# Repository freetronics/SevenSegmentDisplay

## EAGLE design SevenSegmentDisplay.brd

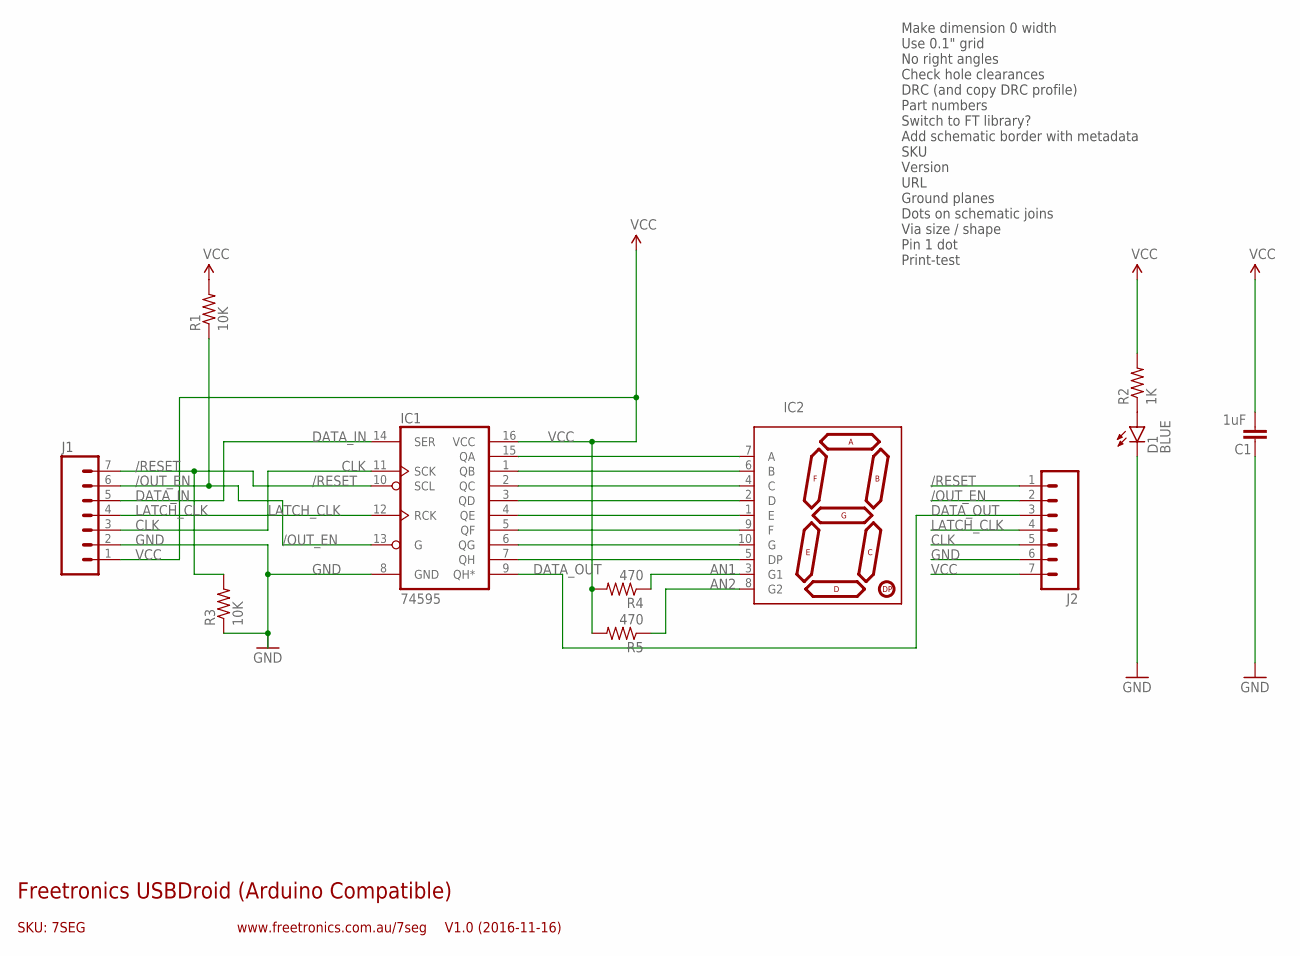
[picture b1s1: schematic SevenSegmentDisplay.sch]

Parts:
C1: 1uF; 0603-CAP
D1: BLUE; LED-0603
IC1: 74595; TSSOP16
IC2: 7-SEGMENT-DISPLAYPTH; 7-SEGMENT-DISPLAY
J1, J2: M07; 1X07
R1, R3: 10K; 0603-RES
R2: 1K; 0603-RES
R4, R5: 470; 0603-RES

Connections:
/OUT_EN: IC1.13 (G), J1.6, J2.2, R1.1
/RESET: IC1.10 (SCL), J1.7, J2.1, R3.2
AN1: IC2.3 (G1), R4.1
AN2: IC2.8 (G2), R5.1
CLK: IC1.11 (SCK), J1.3, J2.5
DATA_IN: IC1.14 (SER), J1.5
DATA_OUT: IC1.9 (QH*), J2.3
GND: C1.1, D1.C, IC1.8 (GND), J1.2, J2.6, R3.1
LATCH_CLK: IC1.12 (RCK), J1.4, J2.4
unnamed: IC1.15 (QA), IC2.7 (A)
unnamed: IC1.1 (QB), IC2.6 (B)
unnamed: IC1.2 (QC), IC2.4 (C)
unnamed: D1.A, R2.1
unnamed: IC1.3 (QD), IC2.2 (D)
unnamed: IC1.4 (QE), IC2.1 (E)
unnamed: IC1.5 (QF), IC2.9 (F)
unnamed: IC1.6 (QG), IC2.10 (G)
unnamed: IC1.7 (QH), IC2.5 (DP)
VCC: C1.2, IC1.16 (VCC), J1.1, J2.7, R1.2, R2.2, R4.2, R5.2

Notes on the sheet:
Make dimension 0 width Use 0.1" grid No right angles Check hole clearances DRC (and copy DRC profile) Part numbers Switch to FT library? Add schematic border with metadata SKU Version URL Ground planes Dots on schematic joins Via size / shape Pin 1 dot Print-test
Freetronics USBDroid (Arduino Compatible)
V1.0 (2016-11-16)
www.freetronics.com.au/7seg
SKU: 7SEG
IC2

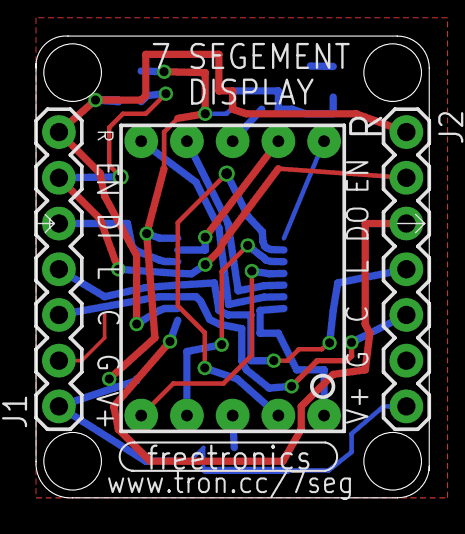
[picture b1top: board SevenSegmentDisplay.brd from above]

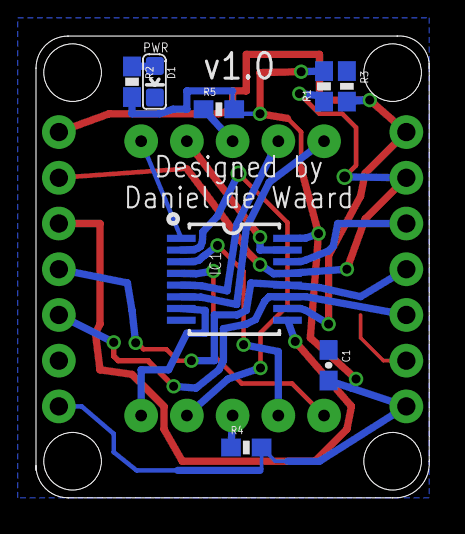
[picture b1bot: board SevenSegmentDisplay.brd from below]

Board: 2 copper layers, 21.8 x 25.7 mm, 11 parts (8 on the bottom side), 19 nets.

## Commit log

2019-04-24 Imported Daniel's design from 2016

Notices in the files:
parts and their libraries:
SparkFun-Capacitors: Licensing: Creative Commons ShareAlike 4.0 International - https://creativecommons.org/licenses/by-sa/4.0
